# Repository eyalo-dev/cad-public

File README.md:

This is my public CAD/PCB file.
Mostly from old magazines and some of my own.
These are not an exact copy but functionaly similar to the original magazine artical.
I also try to make the PCBs smaller than 100mm by 100mm, when possible, as this seem to be 
the entry level pricing in most PCB fabrication places.

Note that all files created using Kicad 5.0.

Free to use on your own risk.

Decoration
Decoration/fun, ball shap (christmas ornament), blinking LEDs
Elektor 2003-12 p. 104

EE-83-function
Function generator
Everyday Electronics 1983-04 p.14 (205)

EE-83-PulseGen
Pulse generator
Everyday Electronics 1983-07 p.456 (58)

EE-83-trn_tester
Transistor & Diode Tester
Everyday Electronics 1983-06 p.370 (44)

ElectronicKeyer
based on Popular Electronics-1976-08 (page 44)

elk_pwm_amp
PWM Audio amplifier
Elektor may 1980, p. 25 (23)
No (Elektor) PCB number.

ETI-438
Audio Level (VU) Meter
ETI-1975-12.pdf p.51 (49) (without PCB) 
ETI-1976-Top Projects 4.pdf, p. 17 (26) (reprint with PCB image - small)

Proto_no2
Elek (Elektor) style proto board.

ServoTester
RC Servo Tester
Maplin-Electronics-1987-09-6.pdf, p. 24 (22)

SignalInjector
Battery (4*1.5V) operated analog signal injector.
Elektor May 1984 (Elektor_1984-05.pdf) page 54.
Elektor 301 circuits vol1, p. 71 (#58).

SmoothOperator
Small board to control hoby type servo.
Elektor 2004-06.pdf, p. 38 (38)

SoundGen
Sound Generator. Different siren like sounds with audio amp.
Elektor USA 1990-10.pdf p. 39 (39)

tennis
digikit reactive tennis game replica PCB.

TrainControl
Analog model train power control
Maplin-Electronics-1985-03-05.pdf p.56 (54)

utiliboard
ETI UTILIBOARD - ETI magazine utility PCB (breadboard)
ETI-Top-Projects-Vol-3.pdf pp. 55 (55)

VaiablePowerSupplay
- Variable power supplay 0-50V / 0 - 2A
- Elektor 1980-07-08.pdf, p. 86 (76)
- No PCB ref. no.

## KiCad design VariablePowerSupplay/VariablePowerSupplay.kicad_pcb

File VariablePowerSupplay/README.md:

Name:
- Variable Power Supplay

Description:
- Variable power supplay 0-50V / 0 - 2A

Source reference:
- Elektor 1980-07-08.pdf, p. 86 (76)
- No PCB ref. no.
- National application note.

This is functional similar but not exact copy.
All dimensions were estimated by eye.
Tried to use similar component placment as much as posible, but using only Kicad
standard PCB component footprint library, so dimentions may very.

PCB
- Done edit but
- Not tested

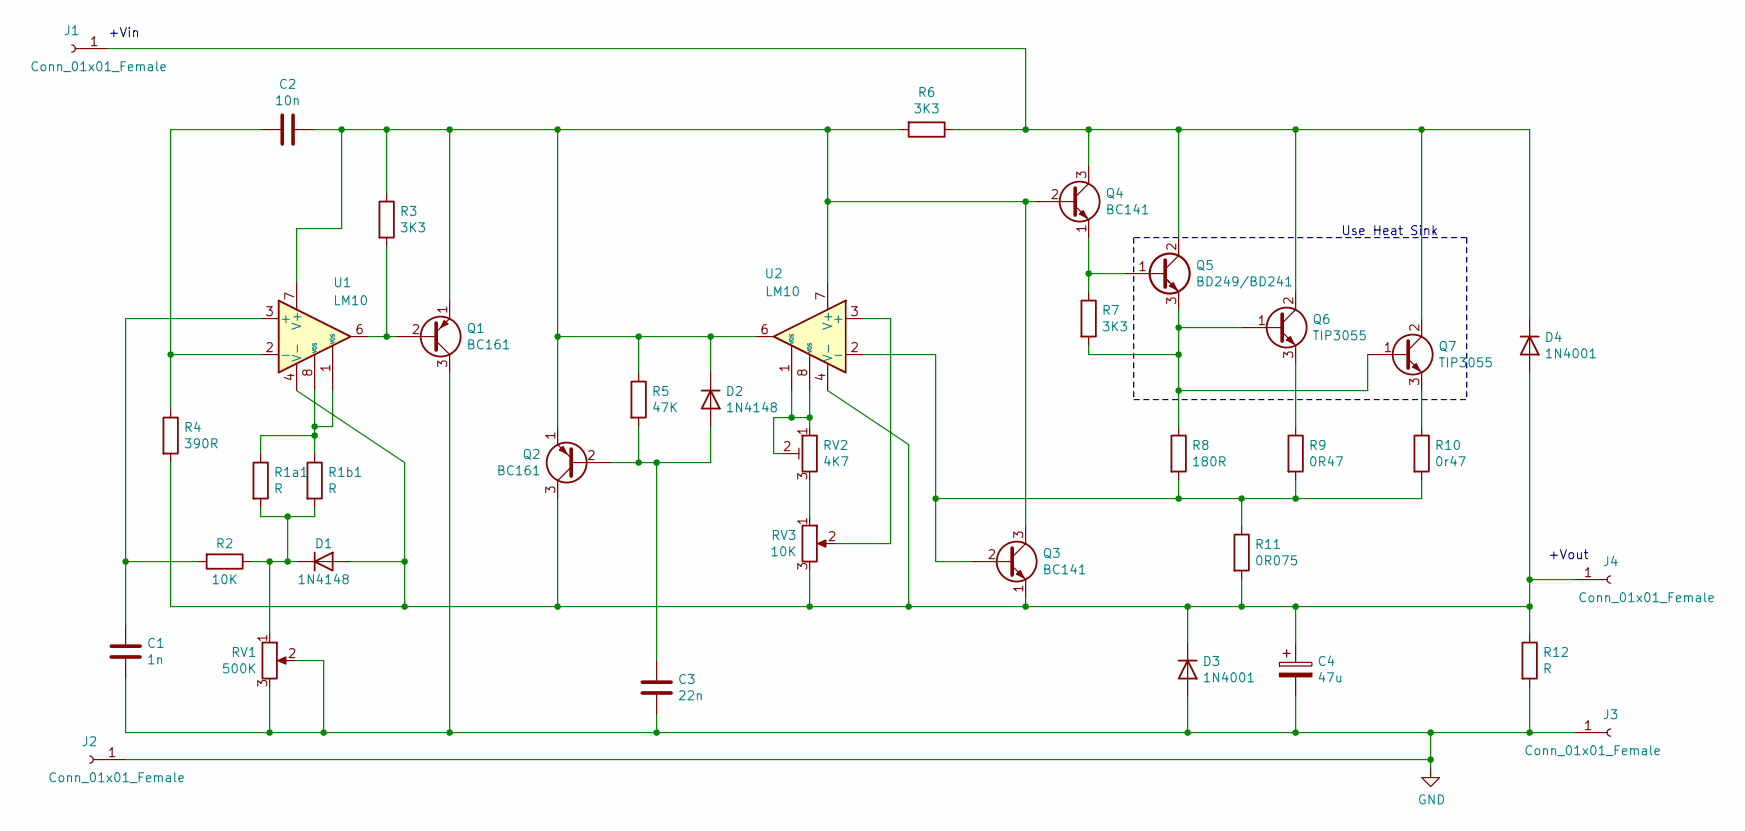
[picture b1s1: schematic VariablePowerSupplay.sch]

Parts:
C1: 1n; C_Disc_D5.0mm_W2.5mm_P5.00mm
C2: 10n; C_Disc_D5.0mm_W2.5mm_P5.00mm
C3: 22n; C_Disc_D5.0mm_W2.5mm_P5.00mm
C4: 47u; CP_Axial_L11.0mm_D6.0mm_P18.00mm_Horizontal
D1, D2: 1N4148; D_DO-35_SOD27_P7.62mm_Horizontal
D3, D4: 1N4001; D_DO-41_SOD81_P10.16mm_Horizontal
J1, J2, J3, J4: Conn_01x01_Female; TestPoint_THTPad_D2.0mm_Drill1.0mm
Q1, Q2: BC161; TO-39-3
Q3, Q4: BC141; TO-39-3
Q5: BD249/BD241; TO-126-3_Vertical
Q6, Q7: TIP3055; TO-218-3_Vertical
R1a1, R1b1: R; R_Axial_DIN0207_L6.3mm_D2.5mm_P10.16mm_Horizontal
R2: 10K; R_Axial_DIN0207_L6.3mm_D2.5mm_P10.16mm_Horizontal
R3, R7: 3K3; R_Axial_DIN0207_L6.3mm_D2.5mm_P10.16mm_Horizontal
R4: 390R; R_Axial_DIN0207_L6.3mm_D2.5mm_P10.16mm_Horizontal
R5: 47K; R_Axial_DIN0207_L6.3mm_D2.5mm_P10.16mm_Horizontal
R6: 3K3; R_Axial_DIN0207_L6.3mm_D2.5mm_P15.24mm_Horizontal
R8: 180R; R_Axial_DIN0207_L6.3mm_D2.5mm_P10.16mm_Horizontal
R9: 0R47; R_Axial_DIN0918_L18.0mm_D9.0mm_P25.40mm_Horizontal
R10: 0r47; R_Axial_DIN0918_L18.0mm_D9.0mm_P25.40mm_Horizontal
R11: 0R075; R_Axial_DIN0918_L18.0mm_D9.0mm_P25.40mm_Horizontal
R12: R
RV1: 500K; PinHeader_1x03_P2.54mm_Vertical
RV2: 4K7; Potentiometer_ACP_CA9-V10_Vertical
RV3: 10K; PinHeader_1x03_P2.54mm_Vertical
U1, U2: LM10; DIP-8_W7.62mm_Socket_LongPads

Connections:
GND: C1.1, C3.1, C4.2, D3.2 (A), J2.1, J3.1, Q1.3 (C), R12.2, RV1.2, RV1.3
unnamed: C1.2, R2.2, U1.3 (+)
unnamed: C2.1, D2.1 (K), Q1.1 (E), Q2.1 (E), Q3.3 (C), Q4.2 (B), R3.1, R5.1, R6.2, U1.7 (V+), U2.6, U2.7 (V+)
unnamed: C2.2, R4.1, U1.2 (-)
unnamed: C3.2, D2.2 (A), Q2.2 (B), R5.2
unnamed: C4.1, D1.2 (A), D3.1 (K), D4.2 (A), J4.1, Q2.3 (C), Q3.1 (E), R4.2, R11.2, R12.1, RV3.3, U1.4 (V-), U2.4 (V-)
unnamed: D1.1 (K), R1a1.2, R1b1.2, R2.1, RV1.1
unnamed: D4.1 (K), J1.1, Q4.3 (C), Q5.2 (C), Q6.2 (C), Q7.2 (C), R6.1
unnamed: Q1.2 (B), R3.2, U1.6
unnamed: Q3.2 (B), R8.2, R9.2, R10.2, R11.1, U2.2 (-)
unnamed: Q4.1 (E), Q5.1 (B), R7.1
unnamed: Q5.3 (E), Q6.1 (B), Q7.1 (B), R7.2, R8.1
unnamed: Q6.3 (E), R9.1
unnamed: Q7.3 (E), R10.1
unnamed: R1a1.1, R1b1.1, U1.1 (VOS), U1.8 (VOS)
unnamed: RV2.1, RV2.2, U2.1 (VOS), U2.8 (VOS)
unnamed: RV2.3, RV3.1
unnamed: RV3.2, U2.3 (+)

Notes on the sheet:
+Vin
+Vout
Use Heat Sink

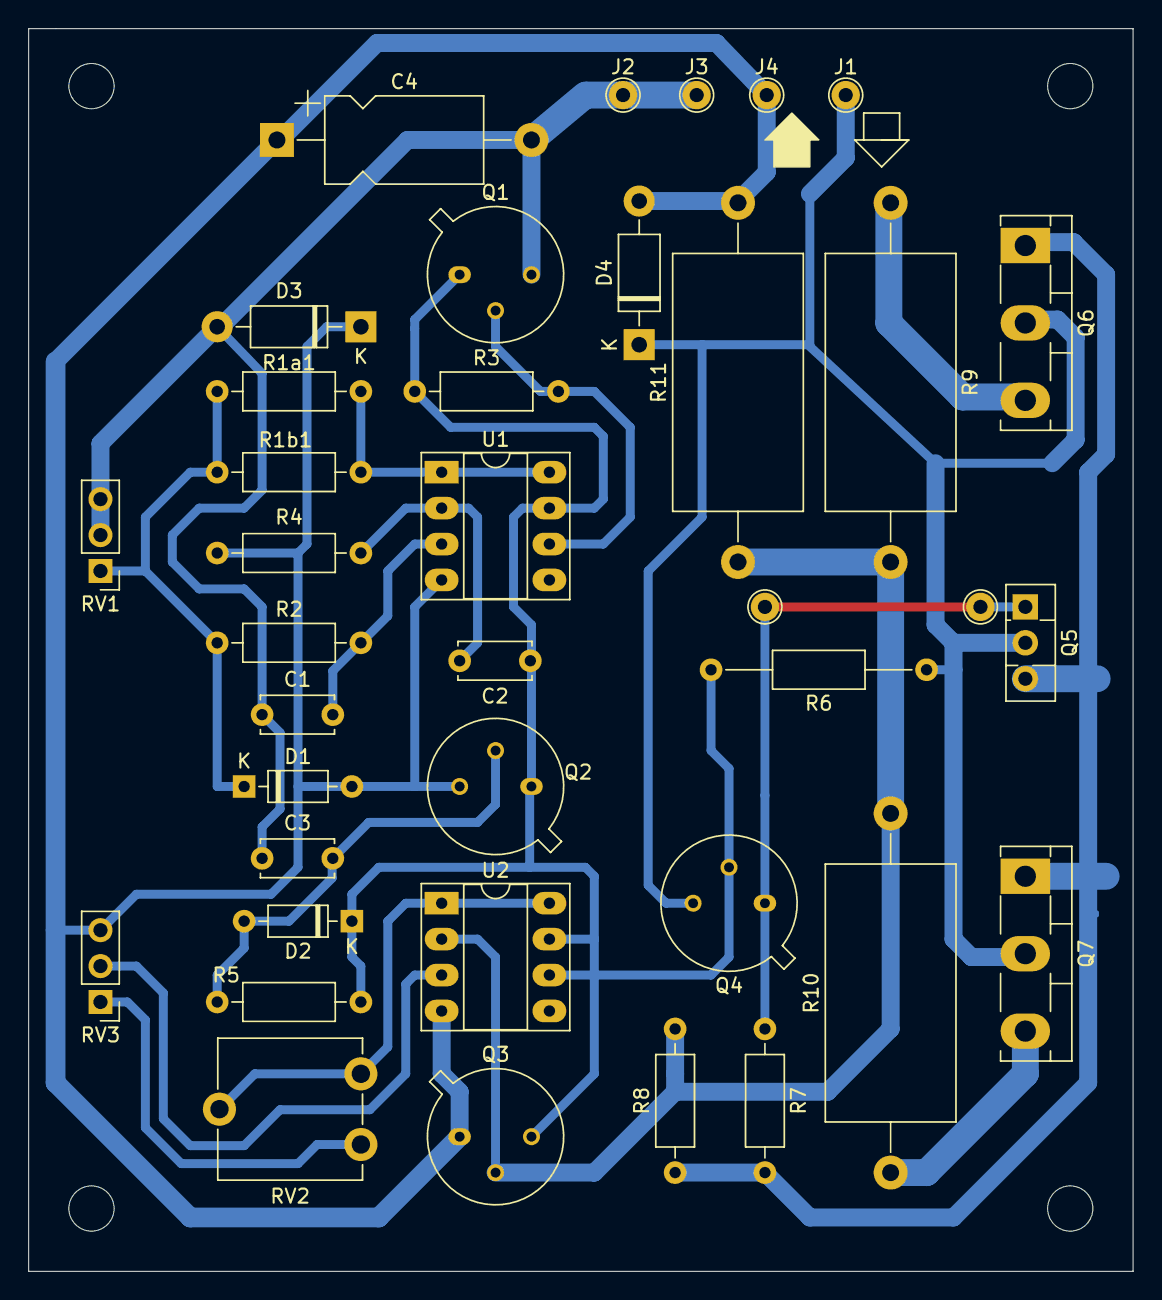
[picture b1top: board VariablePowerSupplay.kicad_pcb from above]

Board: 2 copper layers, 78.1 x 87.9 mm, 36 parts (0 on the bottom side), 18 nets.

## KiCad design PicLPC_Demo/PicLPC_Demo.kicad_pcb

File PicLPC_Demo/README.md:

Name:
- PIC Low Pin Count Demo 

Description:
- Demo board to PIC low (<=20) pin count CPUs

Source reference:
- 

This is functional similar but not exact copy.
All dimension were estimated by eye.
Tried to use similar component placment as much as posible, but using only Kicad
standard PCB component footprint library, so dimentions may very.

PCB
- Done edit but
- Not tested

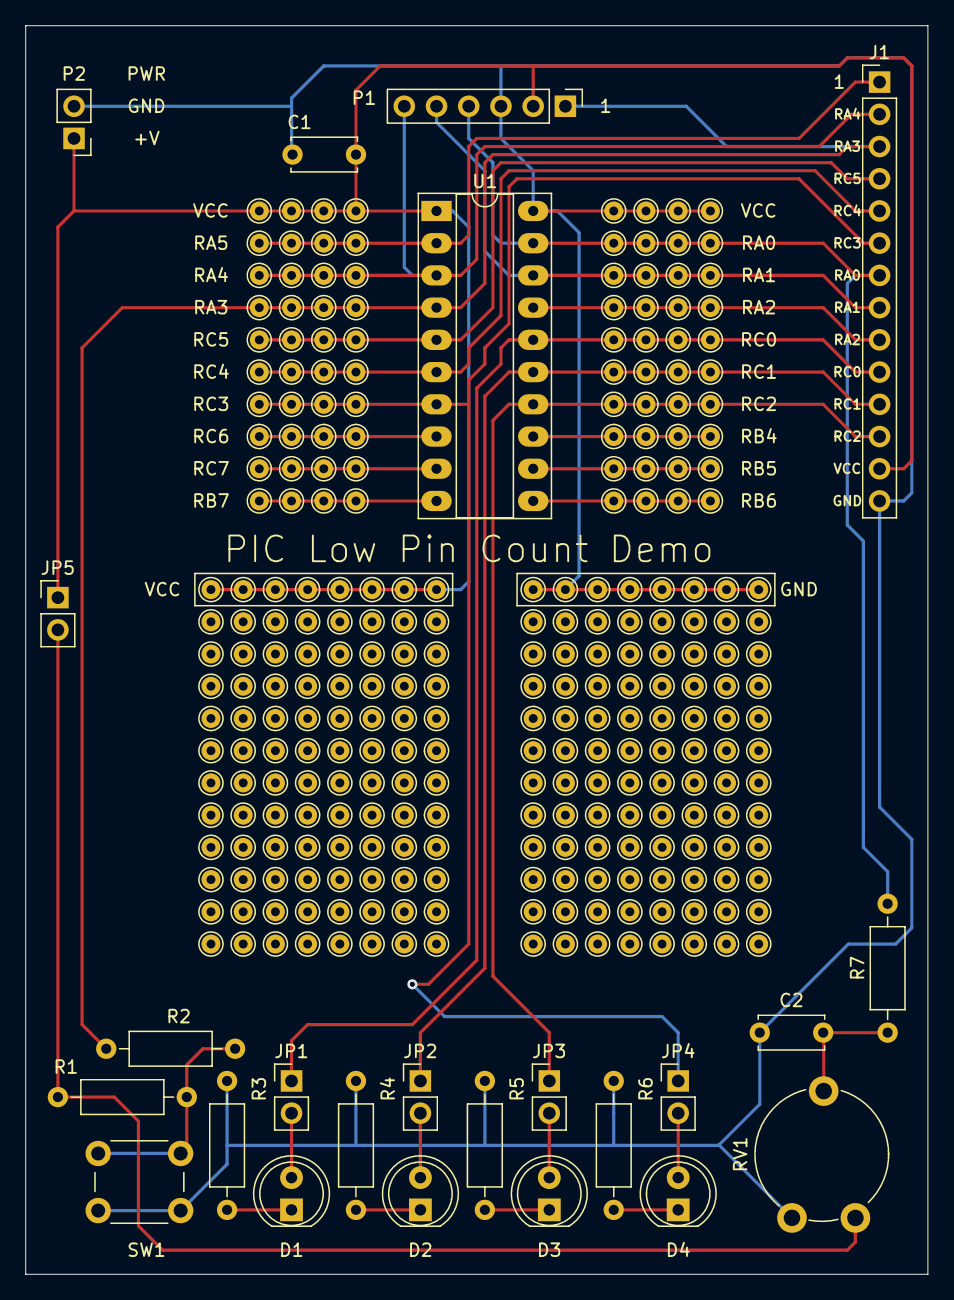
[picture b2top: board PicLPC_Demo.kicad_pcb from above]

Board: 2 copper layers, 71.1 x 98.4 mm, 24 parts (0 on the bottom side), 25 nets.

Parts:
C1, C2: 0.1uF; C_Disc_D5.0mm_W2.5mm_P5.00mm
D1, D2, D3, D4: LED; LED_D5.0mm_Clear
J1: Conn_01x14_Female; PinHeader_1x14_P2.54mm_Vertical
JP1, JP2, JP3, JP4, JP5: Jumper_NO_Small; PinHeader_1x02_P2.54mm_Vertical
P1: Conn_01x06_Male; PinHeader_1x06_P2.54mm_Vertical
P2: PWR; PinHeader_1x02_P2.54mm_Vertical
R1: 10K; R_Axial_DIN0207_L6.3mm_D2.5mm_P10.16mm_Horizontal
R2, R7: 1K; R_Axial_DIN0207_L6.3mm_D2.5mm_P10.16mm_Horizontal
R3, R4, R5, R6: 470R; R_Axial_DIN0207_L6.3mm_D2.5mm_P10.16mm_Horizontal
RV1: 10K; Potentiometer_Piher_PT-10-V10_Vertical
SW1: SW_SPST; SW_PUSH_6mm
U1: PIC16F685-IP; DIP-20_W7.62mm_Socket_LongPads

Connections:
GND: C1.2, C2.2, J1.14, P1.3, P2.2, R3.1, R4.1, R5.1, R6.1, RV1.3, SW1.2, U1.20
unnamed: C2.1, R7.1, RV1.2
unnamed: D1.1, R3.2
unnamed: D1.2, JP1.2
unnamed: D2.1, R4.2
unnamed: D2.2, JP2.2
unnamed: D3.1, R5.2
unnamed: D3.2, JP3.2
unnamed: D4.1, R6.2
unnamed: D4.2, JP4.2
unnamed: JP5.2, R1.1, RV1.1
unnamed: R1.2, R2.1, SW1.1
RA0: J1.7, P1.4, R7.2, U1.19
RA1: J1.8, P1.5, U1.18
RA2: J1.9, U1.17
RA3: J1.3, P1.1, R2.2, U1.4
RA4: J1.2, P1.6, U1.3
RA5: J1.1, U1.2
RC0: J1.10, JP1.1, U1.16
RC1: J1.11, JP2.1, U1.15
RC2: J1.12, JP3.1, U1.14
RC3: J1.6, JP4.1, U1.7
RC4: J1.5, U1.6
RC5: J1.4, U1.5
VCC: C1.1, J1.13, JP5.1, P1.2, P2.1, U1.1

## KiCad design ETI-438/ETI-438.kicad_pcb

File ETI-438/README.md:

Name:
- ETI-438

Description:
- Audio Level (VU) Meter.

Source reference:
- ETI-1975-12.pdf p.51 (49) (without PCB) 
- ETI-1976-Top Projects 4.pdf, p. 17 (26) (reprint with PCB image - small)

This is functional similar but not exact copy.
All dimension were estimated by eye.
Tried to use similar component placment as much as posible, but using only Kicad
standard PCB component footprint library, so dimentions may very.

PCB
- Done edit but
- Not tested

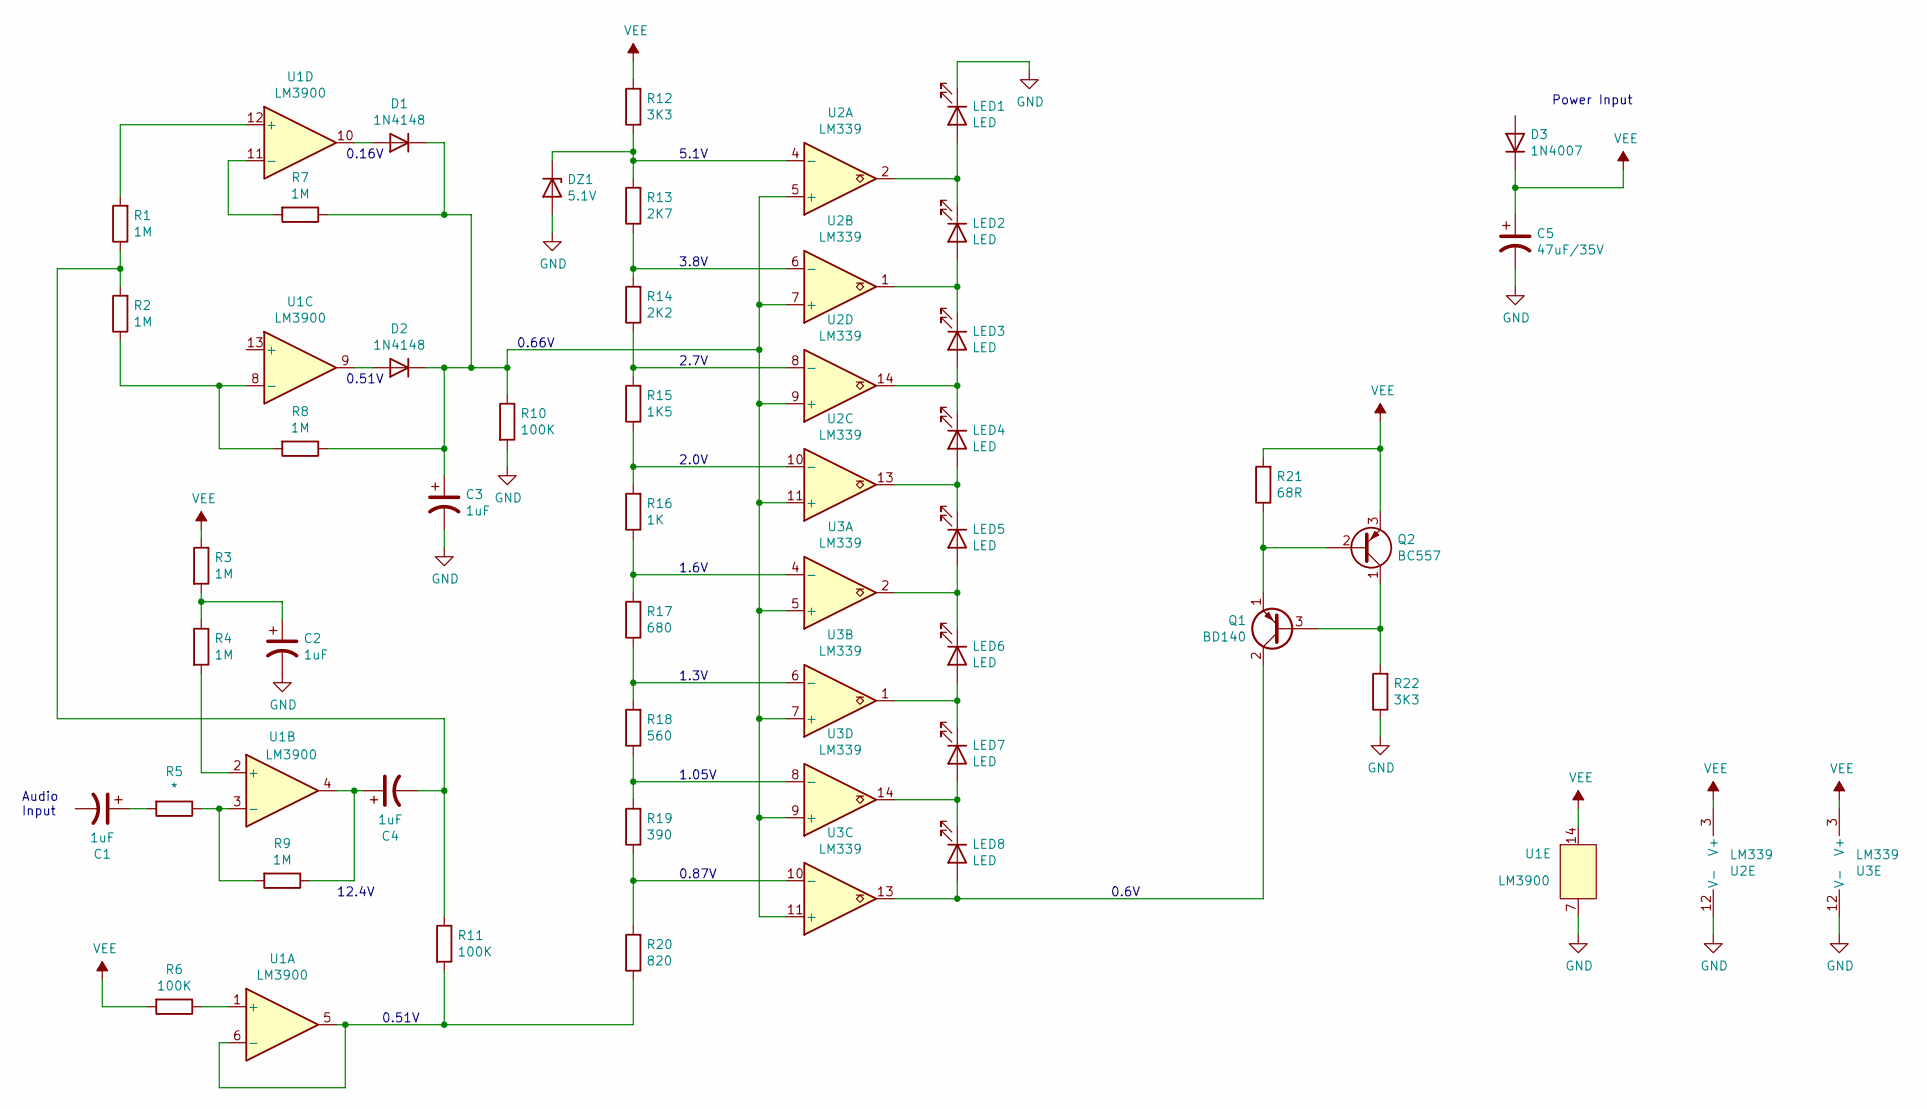
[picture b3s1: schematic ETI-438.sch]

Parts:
C1, C2, C3, C4: 1uF; CP_Radial_D8.0mm_P5.00mm
C5: 47uF/35V; CP_Radial_D8.0mm_P5.00mm
D1, D2: 1N4148; D_DO-35_SOD27_P7.62mm_Horizontal
D3: 1N4007; D_DO-35_SOD27_P7.62mm_Horizontal
DZ1: 5.1V; D_DO-35_SOD27_P7.62mm_Horizontal
LED1, LED2, LED3, LED4, LED5, LED6, LED7, LED8: LED; LED_D5.0mm_Clear
Q1: BD140; TO-126-3_Horizontal_TabUp
Q2: BC557; TO-39-3
R1, R2, R3, R4, R7, R8, R9: 1M; R_Axial_DIN0309_L9.0mm_D3.2mm_P12.70mm_Horizontal
R5: *; R_Axial_DIN0309_L9.0mm_D3.2mm_P12.70mm_Horizontal
R6, R10, R11: 100K; R_Axial_DIN0309_L9.0mm_D3.2mm_P12.70mm_Horizontal
R12, R22: 3K3; R_Axial_DIN0309_L9.0mm_D3.2mm_P12.70mm_Horizontal
R13: 2K7; R_Axial_DIN0309_L9.0mm_D3.2mm_P12.70mm_Horizontal
R14: 2K2; R_Axial_DIN0309_L9.0mm_D3.2mm_P12.70mm_Horizontal
R15: 1K5; R_Axial_DIN0309_L9.0mm_D3.2mm_P12.70mm_Horizontal
R16: 1K; R_Axial_DIN0309_L9.0mm_D3.2mm_P12.70mm_Horizontal
R17: 680; R_Axial_DIN0309_L9.0mm_D3.2mm_P12.70mm_Horizontal
R18: 560; R_Axial_DIN0309_L9.0mm_D3.2mm_P12.70mm_Horizontal
R19: 390; R_Axial_DIN0309_L9.0mm_D3.2mm_P12.70mm_Horizontal
R20: 820; R_Axial_DIN0309_L9.0mm_D3.2mm_P12.70mm_Horizontal
R21: 68R; R_Axial_DIN0309_L9.0mm_D3.2mm_P12.70mm_Horizontal
U1: LM3900; DIP-14_W7.62mm_Socket_LongPads
U2, U3: LM339; DIP-14_W7.62mm_Socket_LongPads

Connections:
GND: C2.2, C3.2, C5.2, DZ1.2 (A), LED1.1 (K), R10.2, R22.1, U1.7, U2.12 (V-), U3.12 (V-)
unnamed: C1.1, R5.2
unnamed: C2.1, R3.2, R4.1
unnamed: C3.1, D1.1 (K), D2.1 (K), R7.1, R8.1, R10.1, U2.5 (+), U2.7 (+), U2.9 (+), U2.11 (+), U3.5 (+), U3.7 (+), U3.9 (+), U3.11 (+)
unnamed: C4.1, R9.1, U1.4
unnamed: C4.2, R1.1, R2.2, R11.1
unnamed: D1.2 (A), U1.10
unnamed: D2.2 (A), U1.9
unnamed: DZ1.1 (K), R12.1, R13.2, U2.4 (-)
unnamed: LED1.2 (A), LED2.1 (K), U2.2
unnamed: LED2.2 (A), LED3.1 (K), U2.1
unnamed: LED3.2 (A), LED4.1 (K), U2.14
unnamed: LED4.2 (A), LED5.1 (K), U2.13
unnamed: LED5.2 (A), LED6.1 (K), U3.2
unnamed: LED6.2 (A), LED7.1 (K), U3.1
unnamed: LED7.2 (A), LED8.1 (K), U3.14
unnamed: LED8.2 (A), Q1.2 (C), U3.13
unnamed: Q1.1 (E), Q2.2 (B), R21.1
unnamed: Q1.3 (B), Q2.1 (C), R22.2
unnamed: R1.2, U1.12 (+)
unnamed: R2.1, R8.2, U1.8 (-)
unnamed: R4.2, U1.2 (+)
unnamed: R5.1, R9.2, U1.3 (-)
unnamed: R6.1, U1.1 (+)
unnamed: R7.2, U1.11 (-)
unnamed: R11.2, R20.1, U1.5, U1.6 (-)
unnamed: R13.1, R14.2, U2.6 (-)
unnamed: R14.1, R15.2, U2.8 (-)
unnamed: R15.1, R16.2, U2.10 (-)
unnamed: R16.1, R17.2, U3.4 (-)
unnamed: R17.1, R18.2, U3.6 (-)
unnamed: R18.1, R19.2, U3.8 (-)
unnamed: R19.1, R20.2, U3.10 (-)
VEE: C5.1, D3.1 (K), Q2.3 (E), R3.1, R6.2, R12.2, R21.2, U1.14, U2.3 (V+), U3.3 (V+)

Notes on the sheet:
Audio Input
12.4V
0.51V
0.16V
0.66V
5.1V
3.8V
2.7V
2.0V
1.6V
1.3V
1.05V
0.87V
Power Input
0.6V

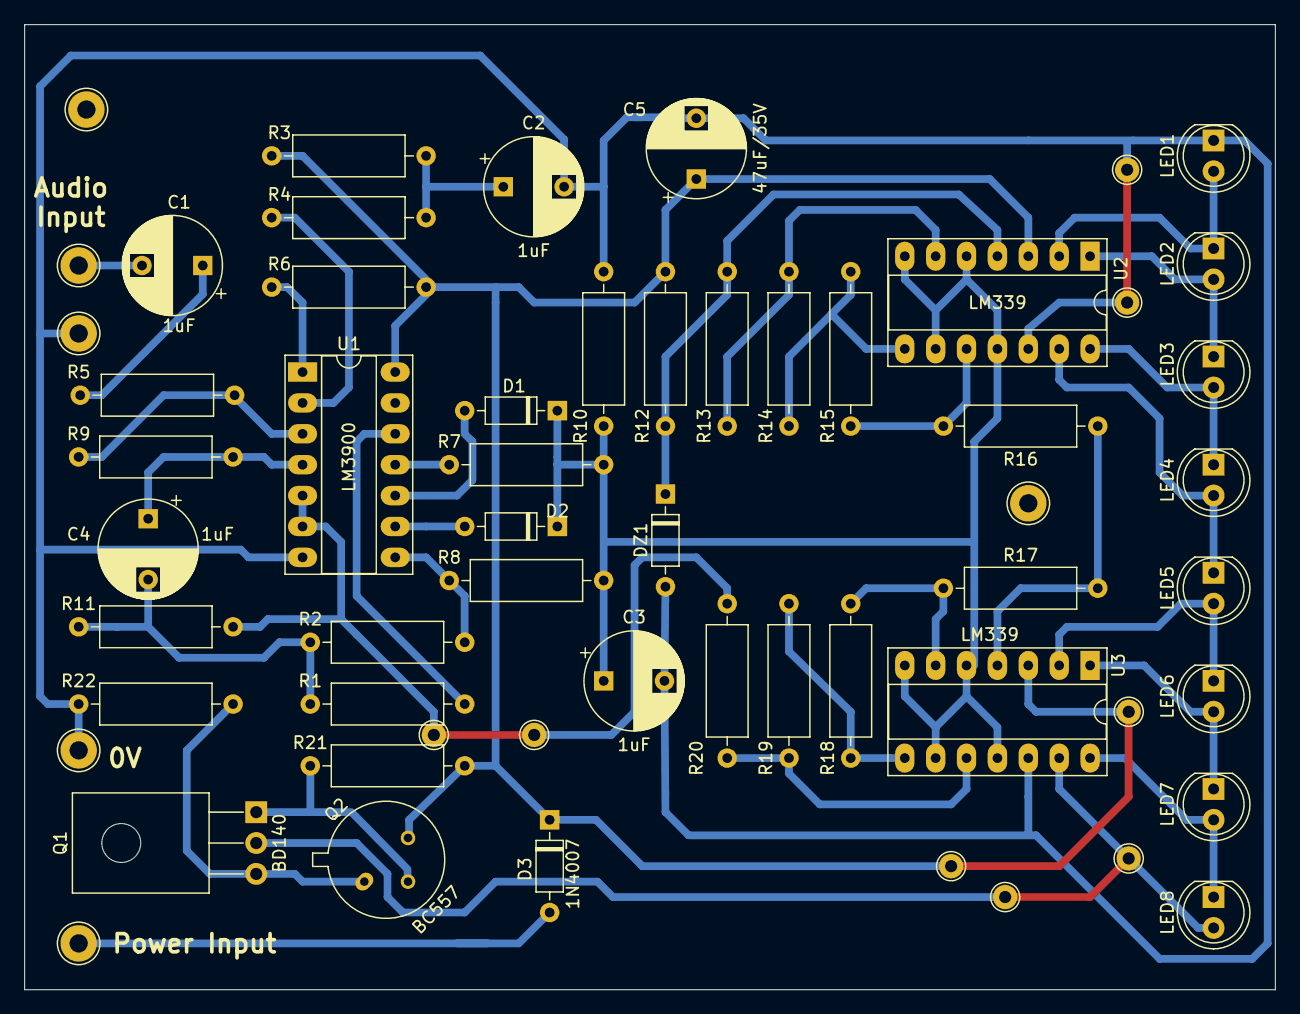
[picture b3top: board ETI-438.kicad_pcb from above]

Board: 2 copper layers, 102.9 x 79.4 mm, 44 parts (0 on the bottom side), 34 nets.

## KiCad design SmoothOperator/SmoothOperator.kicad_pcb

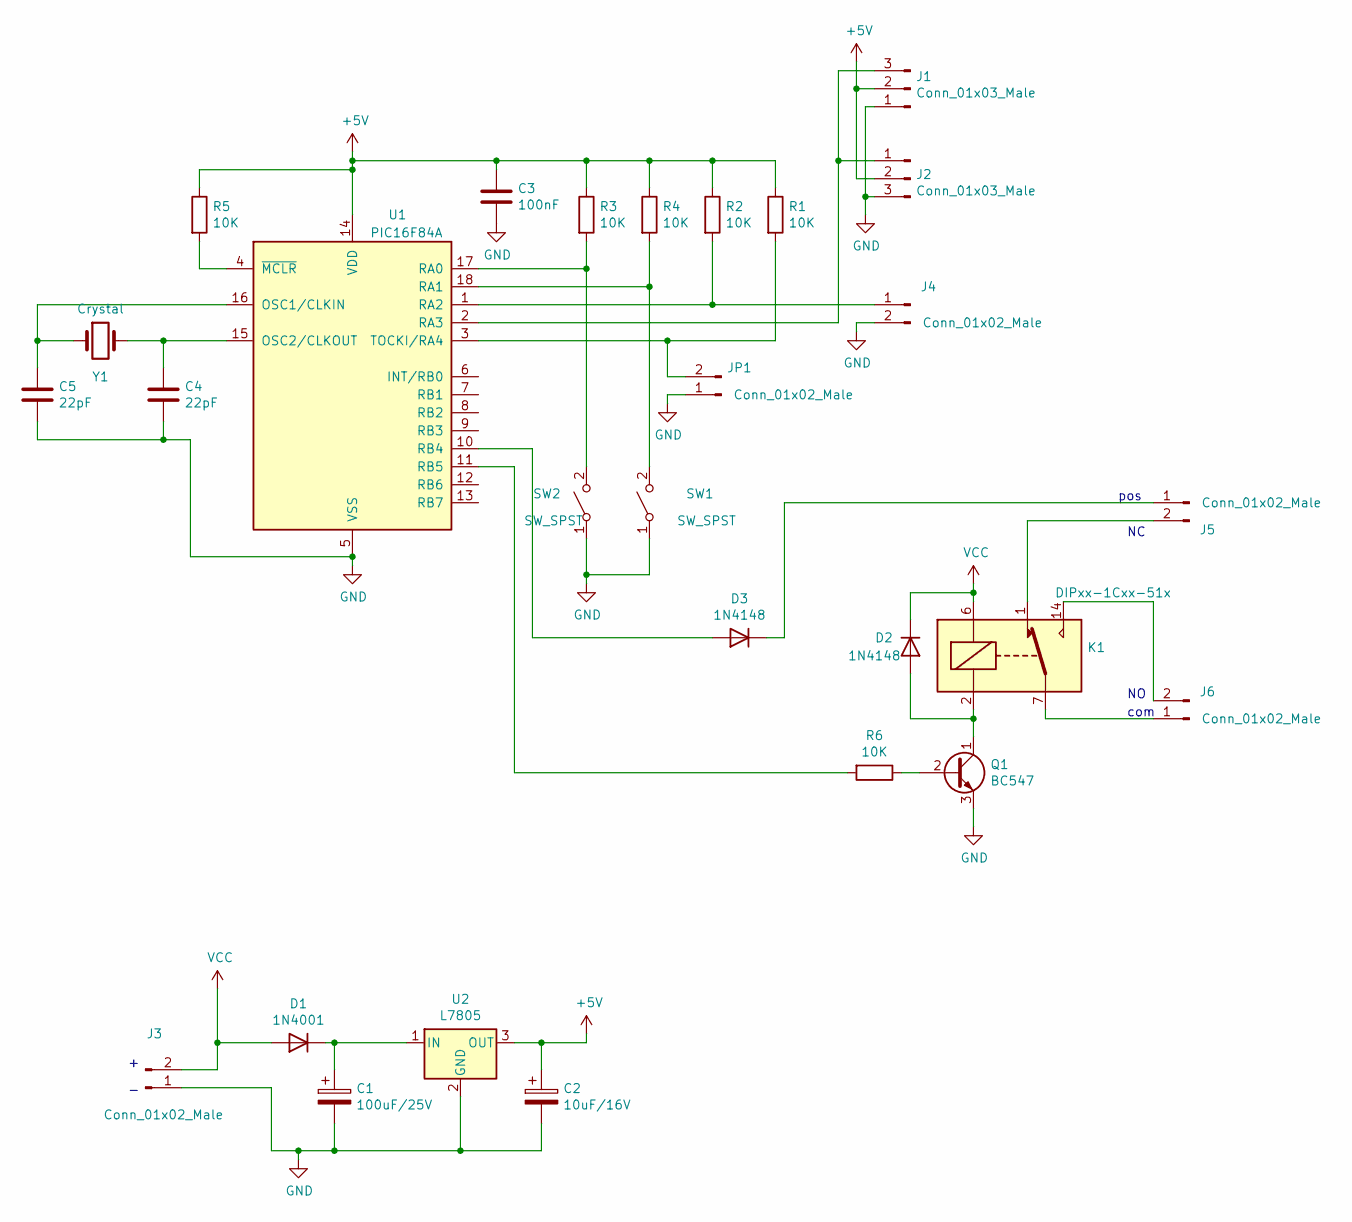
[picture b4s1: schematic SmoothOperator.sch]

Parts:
C1: 100uF/25V; CP_Radial_Tantal_D7.0mm_P5.00mm
C2: 10uF/16V; CP_Radial_Tantal_D7.0mm_P5.00mm
C3: 100nF; C_Disc_D5.0mm_W2.5mm_P5.00mm
C4, C5: 22pF; C_Disc_D5.0mm_W2.5mm_P5.00mm
D1: 1N4001; D_DO-41_SOD81_P10.16mm_Horizontal
D2, D3: 1N4148; D_DO-35_SOD27_P7.62mm_Horizontal
J1: Conn_01x03_Male; PinHeader_1x03_P2.54mm_Vertical
J2: Conn_01x03_Male; TerminalBlock_MetzConnect_Type086_RT03403HBLC_1x03_P3.81mm_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
J3, J4, J5, J6: Conn_01x02_Male; TerminalBlock_MetzConnect_Type086_RT03402HBLC_1x02_P3.81mm_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
JP1: Conn_01x02_Male; PinHeader_1x02_P2.54mm_Vertical
K1: DIPxx-1Cxx-51x; Relay_SPDT_Omron-G5Q-1
Q1: BC547; TO-92_Inline
R1, R2, R3, R4, R5, R6: 10K; R_Axial_DIN0207_L6.3mm_D2.5mm_P10.16mm_Horizontal
SW1, SW2: SW_SPST; SW_PUSH_6mm
U1: PIC16F84A; DIP-18_W7.62mm_Socket_LongPads
U2: L7805; TO-220-3_Vertical
Y1: Crystal; Crystal_HC18-U_Vertical

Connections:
+5V: C2.1, C3.1, J1.2, J2.2, R1.1, R2.1, R3.1, R4.1, R5.1, U1.14 (VDD), U2.3 (OUT)
GND: C1.2, C2.2, C3.2, C4.2, C5.2, J1.1, J2.3, J3.1, J4.2, JP1.1, Q1.3 (E), SW1.1 (A), SW2.1 (A), U1.5 (VSS), U2.2 (GND)
unnamed: C1.1, D1.1 (K), U2.1 (IN)
unnamed: C4.1, U1.15 (OSC2/CLKOUT), Y1.2
unnamed: C5.1, U1.16 (OSC1/CLKIN), Y1.1
unnamed: D2.2 (A), K1.2, Q1.1 (C)
unnamed: D3.1 (K), J5.1
unnamed: D3.2 (A), U1.10 (RB4)
unnamed: J1.3, J2.1, U1.2 (RA3)
unnamed: J4.1, R2.2, U1.1 (RA2)
unnamed: J5.2, K1.1
unnamed: J6.1, K1.7, K1.8
unnamed: J6.2, K1.14
unnamed: JP1.2, R1.2, U1.3 (TOCKI/RA4)
unnamed: Q1.2 (B), R6.1
unnamed: R3.2, SW2.2 (B), U1.17 (RA0)
unnamed: R4.2, SW1.2 (B), U1.18 (RA1)
unnamed: R5.2, U1.4 (~MCLR~)
unnamed: R6.2, U1.11 (RB5)
VCC: D1.2 (A), D2.1 (K), J3.2, K1.6

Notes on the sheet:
pos
com

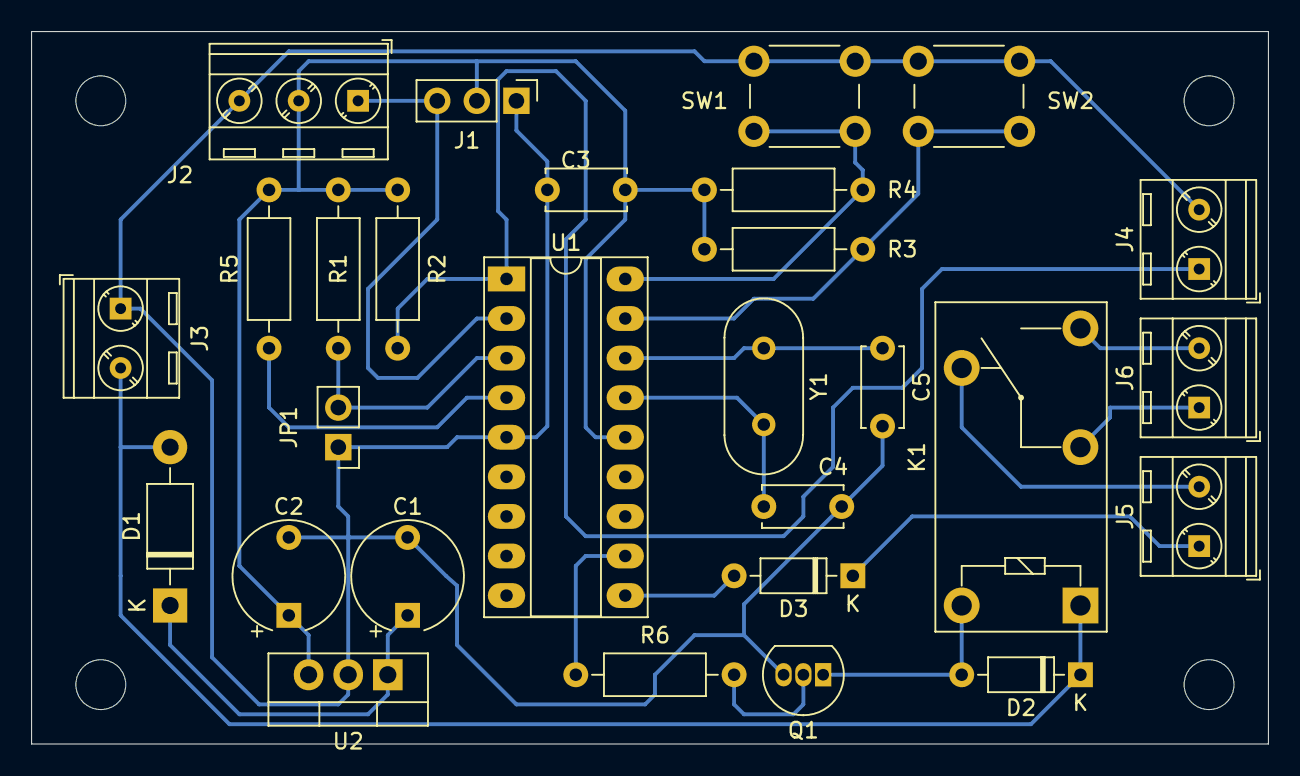
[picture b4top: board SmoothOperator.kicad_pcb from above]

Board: 2 copper layers, 79.4 x 45.7 mm, 28 parts (0 on the bottom side), 20 nets.

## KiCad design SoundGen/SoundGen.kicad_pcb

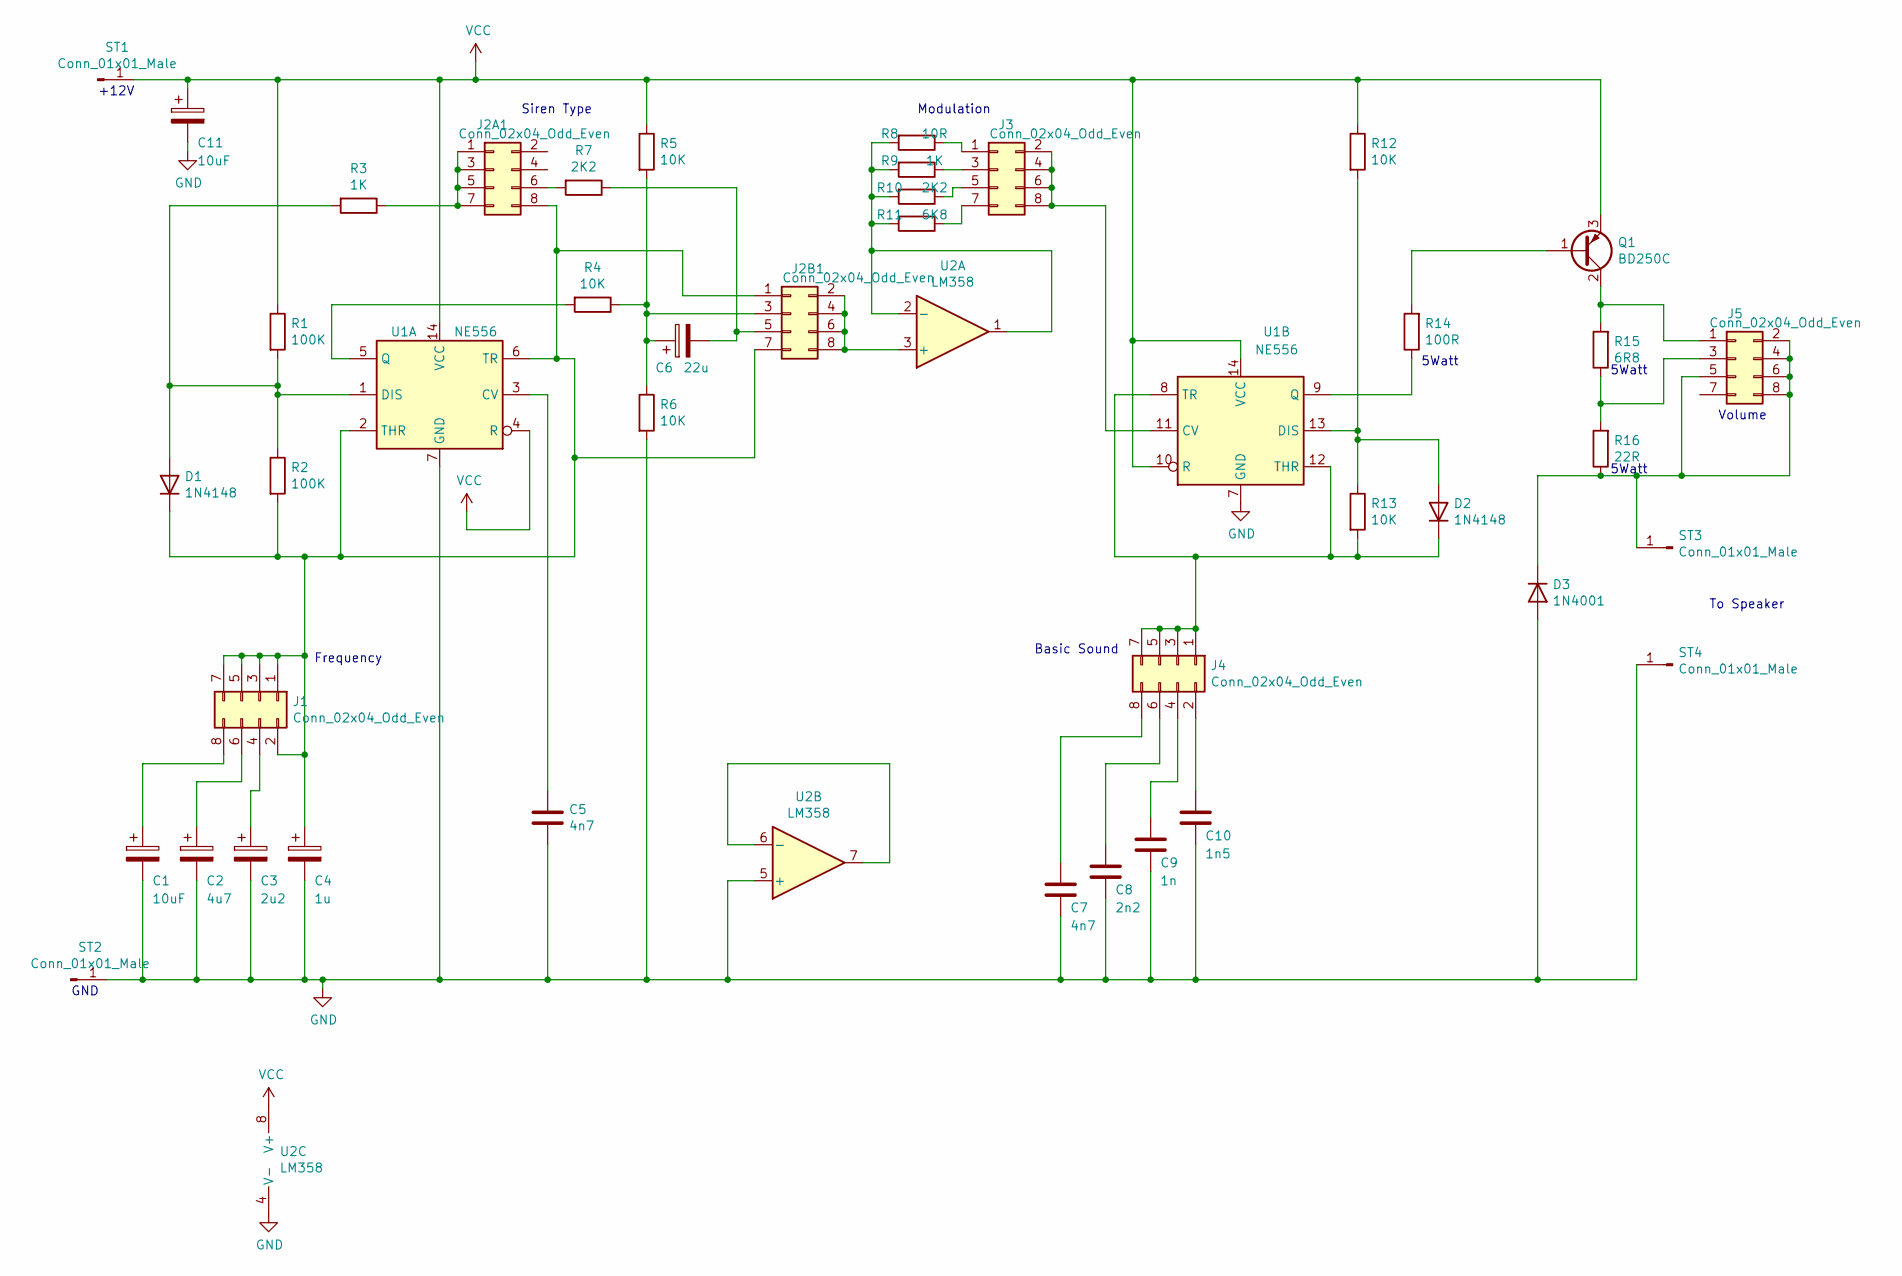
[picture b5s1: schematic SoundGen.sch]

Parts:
C1, C11: 10uF; CP_Radial_Tantal_D7.0mm_P5.00mm
C2: 4u7; CP_Radial_Tantal_D7.0mm_P5.00mm
C3: 2u2; CP_Radial_Tantal_D7.0mm_P5.00mm
C4: 1u; CP_Radial_Tantal_D7.0mm_P5.00mm
C5, C7: 4n7; C_Disc_D5.0mm_W2.5mm_P5.00mm
C6: 22u; CP_Radial_Tantal_D7.0mm_P5.00mm
C8: 2n2; C_Disc_D5.0mm_W2.5mm_P5.00mm
C9: 1n; C_Disc_D5.0mm_W2.5mm_P5.00mm
C10: 1n5; C_Disc_D5.0mm_W2.5mm_P5.00mm
D1, D2: 1N4148; D_DO-35_SOD27_P7.62mm_Horizontal
D3: 1N4001; D_DO-41_SOD81_P10.16mm_Horizontal
J1, J2A1, J2B1, J3, J4, J5: Conn_02x04_Odd_Even; PinHeader_2x04_P2.54mm_Vertical
Q1: BD250C; TO-218-3_Vertical
R1, R2: 100K; R_Axial_DIN0207_L6.3mm_D2.5mm_P10.16mm_Horizontal
R3, R9: 1K; R_Axial_DIN0207_L6.3mm_D2.5mm_P10.16mm_Horizontal
R4, R5, R6, R12, R13: 10K; R_Axial_DIN0207_L6.3mm_D2.5mm_P10.16mm_Horizontal
R7, R10: 2K2; R_Axial_DIN0207_L6.3mm_D2.5mm_P10.16mm_Horizontal
R8: 10R; R_Axial_DIN0207_L6.3mm_D2.5mm_P10.16mm_Horizontal
R11: 6K8; R_Axial_DIN0207_L6.3mm_D2.5mm_P10.16mm_Horizontal
R14: 100R; R_Axial_DIN0617_L17.0mm_D6.0mm_P30.48mm_Horizontal
R15: 6R8; R_Axial_DIN0617_L17.0mm_D6.0mm_P30.48mm_Horizontal
R16: 22R; R_Axial_DIN0617_L17.0mm_D6.0mm_P30.48mm_Horizontal
ST1, ST2, ST3, ST4: Conn_01x01_Male; TestPoint_THTPad_D2.0mm_Drill1.0mm
U1: NE556; DIP-14_W7.62mm_Socket_LongPads
U2: LM358; DIP-8_W7.62mm_Socket_LongPads

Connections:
GND: C1.2, C2.2, C3.2, C4.2, C5.2, C7.2, C8.2, C9.2, C10.2, C11.2, D3.2 (A), R6.2, ST2.1, ST4.1, U1.7 (GND), U2.4 (V-), U2.5 (+)
unnamed: C1.1, J1.8
unnamed: C2.1, J1.6
unnamed: C3.1, J1.4
unnamed: C4.1, D1.1 (K), J1.1, J1.2, J1.3, J1.5, J1.7, J2A1.8, J2B1.1, J2B1.7, R2.2, U1.2 (THR), U1.6 (TR)
unnamed: C5.1, U1.3 (CV)
unnamed: C6.1, J2B1.3, R4.1, R5.2, R6.1
unnamed: C6.2, J2B1.5, R7.1
unnamed: C7.1, J4.8
unnamed: C8.1, J4.6
unnamed: C9.1, J4.4
unnamed: C10.1, J4.2
unnamed: D1.2 (A), R1.2, R2.1, R3.2, U1.1 (DIS)
unnamed: D2.1 (K), J4.1, J4.3, J4.5, J4.7, R13.2, U1.8 (TR), U1.12 (THR)
unnamed: D2.2 (A), R12.2, R13.1, U1.13 (DIS)
unnamed: D3.1 (K), J5.2, J5.4, J5.5, J5.6, J5.8, R16.1, ST3.1
unnamed: J2A1.1, J2A1.3, J2A1.5, J2A1.7, R3.1
unnamed: J2A1.6, R7.2
unnamed: J2B1.2, J2B1.4, J2B1.6, J2B1.8, U2.3 (+)
unnamed: J3.1, R8.1
unnamed: J3.2, J3.4, J3.6, J3.8, U1.11 (CV)
unnamed: J3.3, R9.1
unnamed: J3.5, R10.1
unnamed: J3.7, R11.1
unnamed: J5.1, Q1.2 (C), R15.2
unnamed: J5.3, R15.1, R16.2
unnamed: Q1.1 (B), R14.2
unnamed: R4.2, U1.5 (Q)
unnamed: R8.2, R9.2, R10.2, R11.2, U2.1, U2.2 (-)
unnamed: R14.1, U1.9 (Q)
unnamed: U2.6 (-), U2.7
VCC: C11.1, Q1.3 (E), R1.1, R5.1, R12.1, ST1.1, U1.4 (R), U1.10 (R), U1.14 (VCC), U2.8 (V+)

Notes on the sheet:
Siren Type
Frequency
+12V
GND
Modulation
5Watt
Basic Sound
Volume
To Speaker

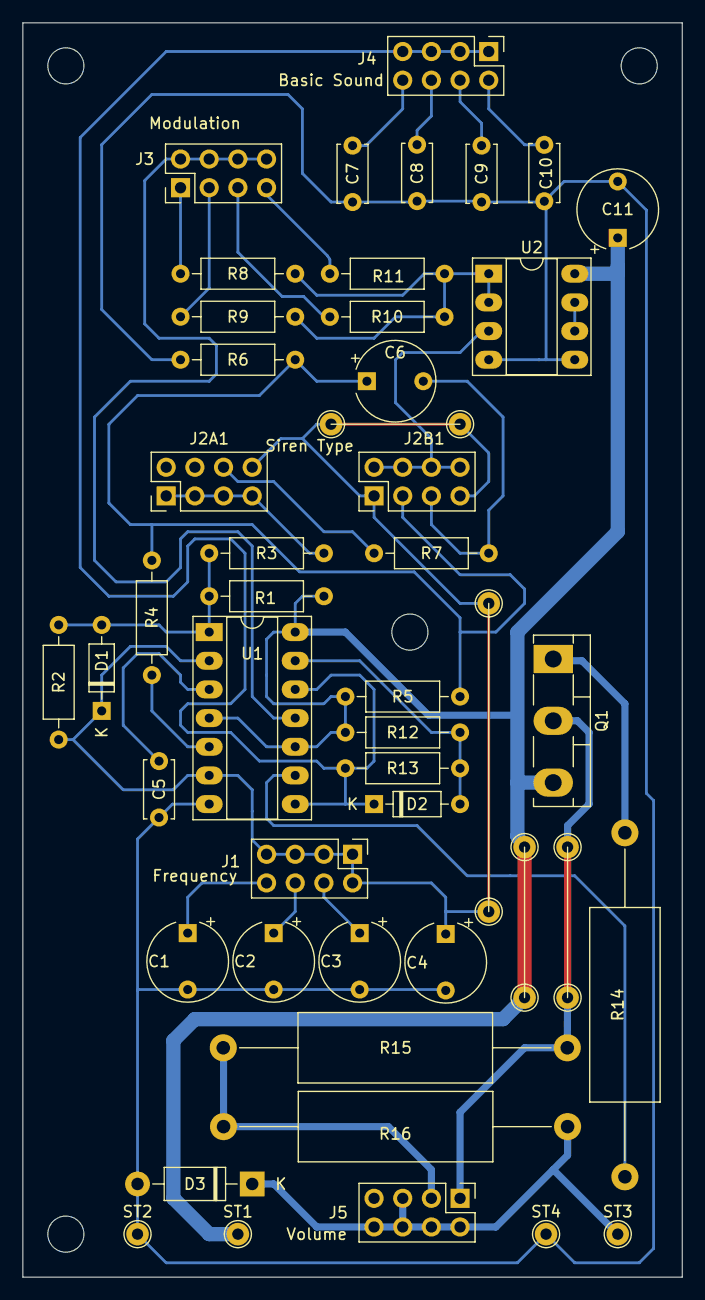
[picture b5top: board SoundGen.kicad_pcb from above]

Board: 2 copper layers, 58.4 x 111.1 mm, 43 parts (0 on the bottom side), 32 nets.
